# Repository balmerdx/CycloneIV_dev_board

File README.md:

# Отладочная плата на Cyclone IV

Это простая отладочная плата для FPGA Cyclone IV EP4CE10.
Кроме собственно FPGA на ней расположенны:
* 4 светодиода
* CP2102 для общения с компьютером по UART
* SPI Flash для записи прошивки
* JTAG
* 28 ножек FPGA для подключения пользовательских устройств

[Схема в pdf формате](https://github.com/balmerdx/CycloneIV_dev_board/blob/master/documentation/cp4ce10_0.pdf)

### Плата в KICAD

### Внешний вид

### Папки

В папке **ep4ce10_0** располагается собственно проект на KiCAD.
В папке examples пара примеров, работающих на ней.

**examples/test_my_board_led** - сравнительно простой пример, который умеет мигать светодиодами и принимать байт с командами по UART (на скорости 115200 bps). Пример общения с компьютером в файле examples/test_my_board_led/test_usart.py . Формат команды простой, посылаем 1 байт на устройство. Младшие 4 бита - состояние светодиодов (включенно/выключенно). Старший бит - переводит устройство в "самостоятельное плавание", когда оно начинает мигать светодиодиками самостоятельно.

**examples/test_my_board_advanced** - более сложный пример. Не только принимает команды по UART, но и отсылает в ответ строку, которую берет из заранее инициализированной памяти.

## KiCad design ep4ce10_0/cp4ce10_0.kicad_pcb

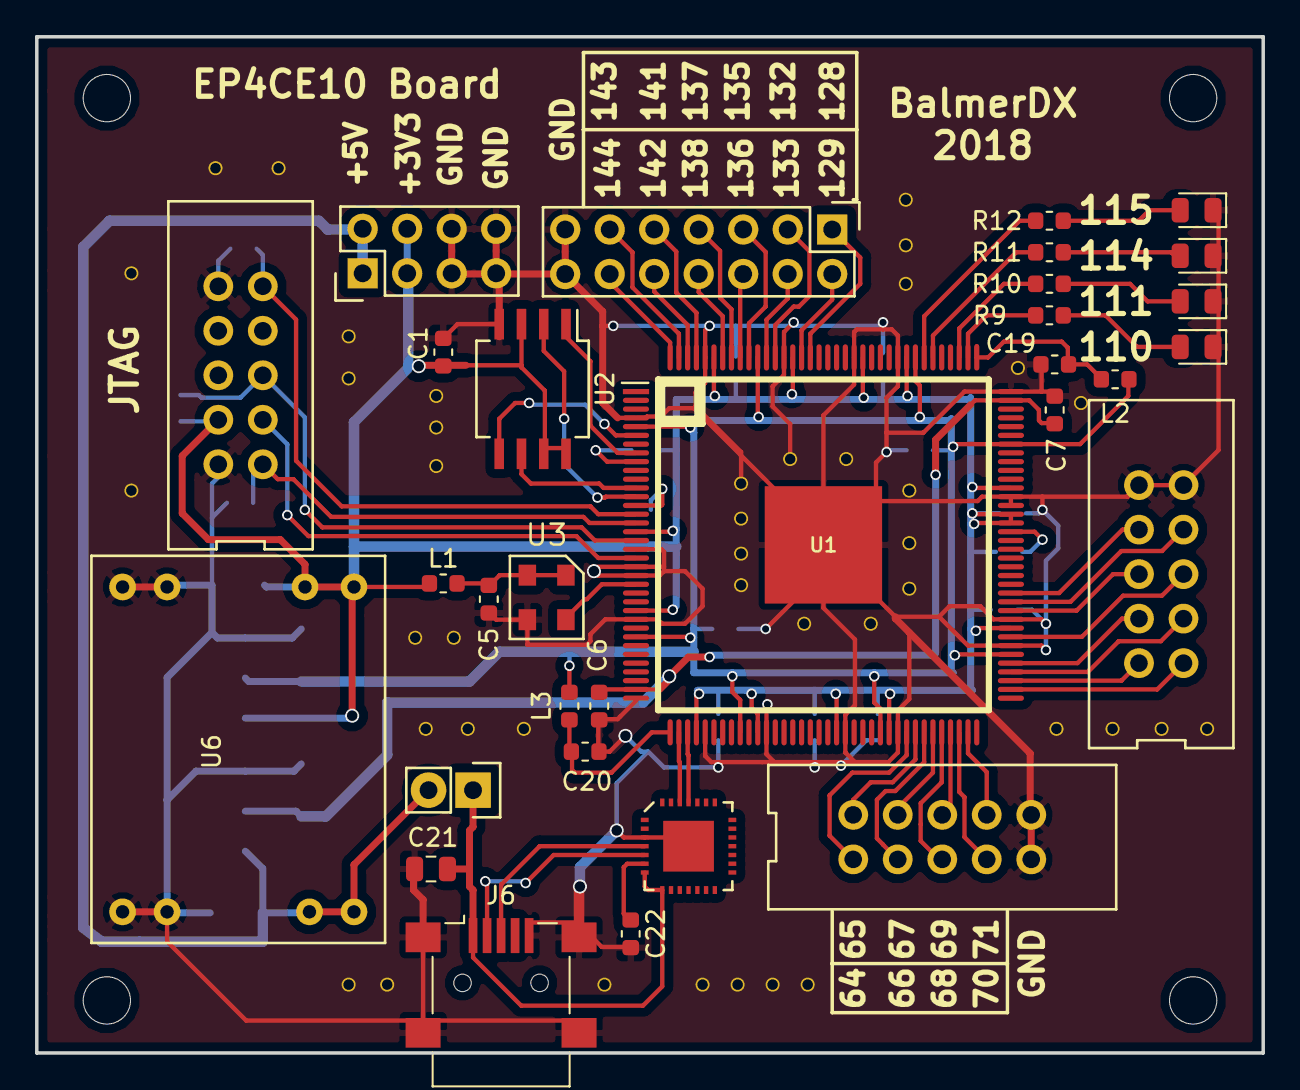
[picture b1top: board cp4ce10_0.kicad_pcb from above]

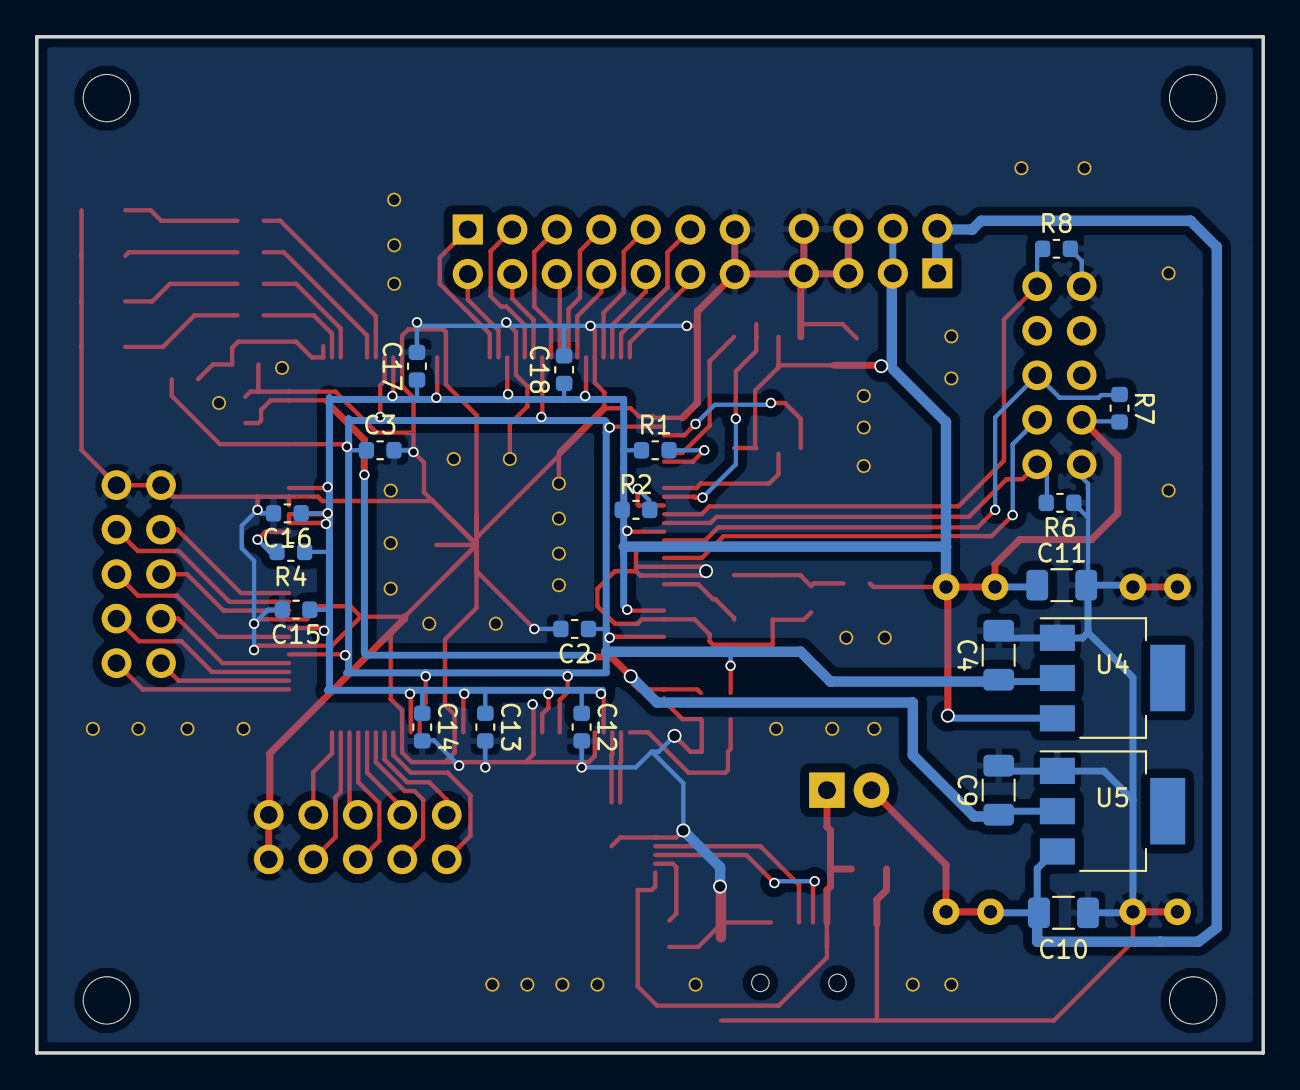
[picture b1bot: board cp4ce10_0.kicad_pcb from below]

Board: 2 copper layers, 70.0 x 58.0 mm, 52 parts (21 on the bottom side), 62 nets.

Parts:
C1, C2, C3, C5, C6, C7, C12, C13, C14, C15, C16, C17, C18, C19, C20, C22: 100n; C_0603_1608Metric
C4, C9, C11: 10u; C_1206_3216Metric
C10: 25u; C_1206_3216Metric
C21: 2.2u; C_0805_2012Metric
D1, D2, D3, D4: LED; LED_0805_2012Metric
J1: BANK5; IDC_10M
J2: BANK8; Pin_Header_Straight_2x07
J3: BANK4; IDC_10M
J4: JTAG; IDC_10M
J5: Conn_01x02; Pin_Header_Straight_1x02
J6: USB_OTG; USB_Mini-B_Lumberg_2486_01_Horizontal
J7: POWER; Pin_Header_Straight_2x04
L1, L2, L3: MMZ1608; C_0603_1608Metric
R1, R2, R4, R7, R8: 10k; R_0603_1608Metric
R6: 1k; R_0603_1608Metric
R9, R10, R11, R12: 510; R_0603_1608Metric
U1: EP4CE6E22; ALTERA-QFP-145
U2: M25P16; SO-8_5.3x6.2mm_P1.27mm
U3: Crystal_Generator; Crystal_5.0x3.2mm
U4: AMS1117-1.2; SOT-223
U5: AMS1117-2.5; SOT-223
U6: SG053-SZ
U7: CP2102; MLP-28

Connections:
5VP: C10.1, J5.2, J7.1, J7.2, U5.3, U6.3
+1V2: C2.1, C3.1, C4.1, L2.1, L3.1, U1.5, U1.29, U1.45, U1.61, U1.78, U1.102, U1.116, U1.134, U4.2
+2V5: C6.1, C7.1, C9.1, U1.35, U1.107, U5.2
+3V3: C1.1, C11.1, C12.1, C13.1, C14.1, C15.1, C16.1, C17.1, C18.1, J4.4, J7.3, J7.4, L1.1, R1.1, R2.1, R4.1, R7.1, U1.17, U1.26, U1.40, U1.47, U1.56, U1.62, U1.81, U1.93, U1.94, U1.97, U1.117, U1.122, U1.130, U1.139, U2.3, U2.7, U2.8, U4.3, U6.4
/64: J3.1, U1.64
/65: J3.2, U1.65
/66: J3.3, U1.66
/67: J3.4, U1.67
/68: J3.5, U1.68
/69: J3.6, U1.69
/70: J3.7, U1.70
/71: J3.8, U1.71
/74: J1.1, U1.74
/75: J1.2, U1.75
/76: J1.3, U1.76
/77: J1.4, U1.77
/80: J1.5, U1.80
/83: J1.6, U1.83
/84: J1.7, U1.84
/85: J1.8, U1.85
/128: J2.1, U1.128
/129: J2.2, U1.129
/132: J2.3, U1.132
/133: J2.4, U1.133
/135: J2.5, U1.135
/136: J2.6, U1.136
/137: J2.7, U1.137
/138: J2.8, U1.138
/141: J2.9, U1.141
/142: J2.10, U1.142
/143: J2.11, U1.143
/144: J2.12, U1.144
/ASDO: U1.6, U2.5
/CLK_50M: U1.23, U3.3
/DATA0: U1.13, U2.2
/DCLK: U1.12, U2.6
/TCK: J4.1, R6.2, U1.16
/TDI: J4.9, R8.1, U1.15
/TDO: J4.3, U1.20
/TMS: J4.5, R7.2, U1.18
/nCs: U1.8, U2.1
GND: C1.2, C2.2, C3.2, C4.2, C5.2, C6.2, C7.2, C9.2, C10.2, C11.2, C12.2, C13.2, C14.2, C15.2, C16.2, C17.2, C18.2, C19.2, C20.2, C21.2, C22.2, D1.1, D2.1, D3.1, D4.1, J1.9, J1.10, J2.13, J2.14, J3.9, J3.10, J4.2, J4.10, J6.5, J6.6, J7.5, J7.6, J7.7, J7.8, R6.1, R8.2, U1.4, U1.19, U1.21, U1.22, U1.27, U1.36, U1.41, U1.48, U1.57, U1.63, U1.79, U1.82, U1.95, U1.96, U1.108, U1.118, U1.123, U1.131, U1.140, U1.145, U2.4, U3.2, U4.1, U5.1, U6.1, U6.2, U7.3
LCD1: R9.2, U1.110
LCD2: R10.2, U1.111
LCD3: R11.2, U1.114
LCD4: R12.2, U1.115
unnamed: C5.1, L1.2, U3.1, U3.4
unnamed: C19.1, L2.2, U1.109
unnamed: C20.1, L3.2, U1.37
unnamed: C21.1, J5.1, J6.1, U7.7, U7.8
unnamed: C22.1, U7.6
unnamed: D1.2, R9.1
unnamed: D2.2, R10.1
unnamed: D3.2, R11.1
unnamed: D4.2, R12.1
unnamed: J6.2, U7.5
unnamed: J6.3, U7.4
unnamed: R1.2, U1.9
unnamed: R2.2, U1.14
unnamed: R4.2, U1.92
RX: U1.39, U7.25
TX: U1.38, U7.26

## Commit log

2018-11-20 KiCAD 5 board files
2018-11-20 Examples LED, UART, Memory Access
2018-11-20 - shots
2018-11-21 schematic pdf
2018-11-24 - питон для com порта
